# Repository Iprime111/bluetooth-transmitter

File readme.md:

# Bluetooth Audio Transmitter  

Портативный Bluetooth-передатчик для беспроводной передачи звука с аналоговых источников (3.5 мм) на наушники или колонки.  
**Цель проекта**: Интеграция проводных аудиоустройств в современные беспроводные экосистемы.

---

## 🚀 Особенности
- **Bluetooth A2DP**: Передача стереозвука с поддержкой кодеков SBC.
- **OLED-дисплей**: SSD1306 (32x64 пикселей) для управления и отображения:
  - Список доступных для подключения устройств.
  - Уровень громкости.
- **Энкодер EC11**: Интуитивное управление (выбор устройств, регулировка громкости).
- **Компактный дизайн**: Корпус 93x61x33 мм, напечатанный на 3D-принтере (PLA).
- **Автономность**: Работа от Li-Po аккумулятора 1050 мАч с зарядкой через USB-C.
- **Открытый исходный код**: Полная документация и файлы для самостоятельной сборки.

---

## 🔧 Технологии и компоненты
### Аппаратная часть
| Компонент               | Характеристики                          | Ссылка на Datasheet |
|-------------------------|-----------------------------------------|---------------------|
| Микроконтроллер         | ESP32-WROOM-32 (Bluetooth 4.2 + Wi-Fi)  | [ESP32-WROOM-32](./docs/esp32-wroom-32_datasheet_en.pdf) |
| АЦП                     | PCM1808 (24-bit, 96 kHz, SNR 112 dB)    | [PCM1808](./docs/pcm1808.pdf)  |
| Драйвер дисплея         | SSD1306 (I2C)                           | [SSD1306](./docs/SSD1306.pdf) |
| Стабилизатор питания    | ADP3338 (3.3V) / L78L05 (5V)            | [ADP3338](./docs/ADP3338.pdf), [L78L05](./docs/l78l-1.pdf) |
| Модуль заряда           | IP2326 (USB-C)                          | [IP2326](./docs/ip2326.pdf) |
| Энкодер                 | EC11                                    | [EC11](./docs/PEC11R.pdf) |

### Программная часть
- **Прошивка**: Написана на C с использованием ESP-IDF v4.4.
- **Библиотеки**:
  - `esp_a2dp` — Реализация Bluetooth A2DP Source (встроенная).
  - `i2s_audio` — Захват аудио с АЦП через I2S (встроенная).
  - `ssd1306` — Управление OLED-дисплеем (написана в рамках проекта).
  - `EC11` — Работа с энкодером (написана в рамках проекта).
- **Инструменты**:
  - `KiCad 7.0` — проектирование схемы и PCB.
  - `Autodesk Inventor` — 3D-моделирование корпуса.
  - `ESP-IDF` — сборка и отладка прошивки.

---

## 📦 Сборка устройства
### 1. Аппаратная часть
#### Схемы и PCB
- [Файлы KiCad](https://github.com/Iprime111/bluetooth-transmitter/tree/master/bluetooth-transmitter-pcb):  
  - Принципиальная схема.  
  - Разводка двухсторонней платы.  
  - Gerber-файлы для заказа на производстве.  

#### 3D-модель корпуса
- [STL и IPT-файлы](https://github.com/Iprime111/bluetooth-transmitter/tree/master/case-design):  
  - Корпус состоит из двух частей: верхняя крышка/корпус с отверстиями для дисплея/энкодера, нижняя — крышка на пазовом соединии.  
  - Рекомендуемые параметры печати: слой 0.2 мм, заполнение 15%.

---

### 2. Программная часть
#### Установка зависимостей
1. Установите [ESP-IDF v5.4](https://docs.espressif.com/projects/esp-idf/en/v5.4.1/esp32/get-started/).
2. Клонируйте репозиторий:
   ```bash
   git clone https://github.com/Iprime111/bluetooth-transmitter.git
   cd bluetooth-transmitter
   ```

#### Компиляция и прошивка
1. Подключите ESP32 через USB.
2. Соберите и загрузите проект:
   ```bash
   idf.py build
   idf.py -p /dev/ttyUSB0 flash
   ```

---

## 🎮 Использование
### Основные функции
1. **Подключение источника звука**:  
   Вставьте кабель 3.5 мм в разъем на корпусе.  
2. **Поиск устройств**:  
   - Включите устройство
   - Нажмите на кнопку энкодера для поиска устройств
   - Поворот энкодера → выбор устройства из списка.  
   - Нажмите энкодер для подключения.
   - При необходимости выберите пункт `RESTART DISCOVER` для повторного сканирования 
3. **Управление громкостью и проигрыванием**:  
   - Выберите пункт `PLAY/STOP` для воспроизведения или остановки аудио
   - Войдите в режим изменения громкости путем выбора соответствующего пункта меню. Поворотом энкодера установите желаемый уровень громкости. Для выхода повторно нажмите кнопку энкодера.  
   - Для отключения нажмите кнопку `BACK`.

---

## 📊 Технические характеристики
| Параметр                | Значение                     |
|-------------------------|------------------------------|
| Радиус действия         | До 15 м (в помещении)        |
| Автономность            | 8 часов (при 50% громкости)  |
| Задержка передачи       | < 200 мс                     |
| Частотный диапазон      | 20 Гц – 20 кГц               |

---

## 🔄 Сравнение с аналогами
| Параметр               | Наш проект             | UGREEN Transmitter     | Sennheiser BT-T100     |
|------------------------|------------------------|------------------------|------------------------|
| **Стоимость**          | ~$20 (DIY)             | ~$40                   | ~$100                  |
| **Размеры**            | 93x61x50 мм            | 80x50x20 мм            | 100x60x25 мм           |
| **Открытость**         | Полная                 | Нет                    | Нет                    |
| **Кастомизация**       | Да (код + корпус)      | Нет                    | Нет                    |

---

## 📁 Структура репозитория
```
bluetooth-transmitter/
├── components/           # Исходный код прошивки (ESP-IDF)
│   ├── audio-stream/     # Получение звука с PCM1808
│   ├── bluetooth-lib/    # GAP, AVRC, A2DP и управление подключениями
│   ├── dispatcher/       # Вспомогательные функции для асинхронной работы
│   ├── oled-display/     # Драйвер SSD1306
│   ├── main/             # Конфигурация устройства и пользовательский интерфейс
│   └── encoder/          # Обработка энкодера
├── bluetooth-transmitter-pcb/  # Схемы и PCB (KiCad)
├── case-design/          # 3D-модели корпуса (IPT, STL)
├── docs/                 # Документация
└── README.md             # Этот файл
```

---

## 📜 Лицензия
Проект распространяется под лицензией **MIT**.  
Полный текст доступен в файле [LICENSE](LICENSE).

---

## 👥 Команда
- **Владимир Чурсин**  
  - Разработка ПО, 3D-моделирование.  
  - ✉️ `chursin.vv@phystech.edu`  
  - [GitHub](https://github.com/Amlola)  
- **Максим Тимошкин**  
  - Схемотехника, сборка, тестирование.  
  - ✉️ `timoshkin.ma@phystech.edu`  
  - [GitHub](https://github.com/Iprime111)  

---

## 📸 Фото и демонстрация
**Фотография финальной версии устройства**

**Фотография прототипа**

**Демонстрация работы**:

<video width="480" height="640" controls>
  <source src="docs/demonstration.mp4" type="video/mp4">
</video>

[Ссылка, если видео не отображается на github](./docs/demonstration.mp4)

---

## 🔮 Будущие улучшения
- Добавление поддержки кодеков aptX.  
- Реализация мультиподключения (2 устройства).  
- Интеграция с мобильным приложением для настройки.  

---

**🔗 Ссылка на проект**: [GitHub](https://github.com/Iprime111/bluetooth-transmitter)

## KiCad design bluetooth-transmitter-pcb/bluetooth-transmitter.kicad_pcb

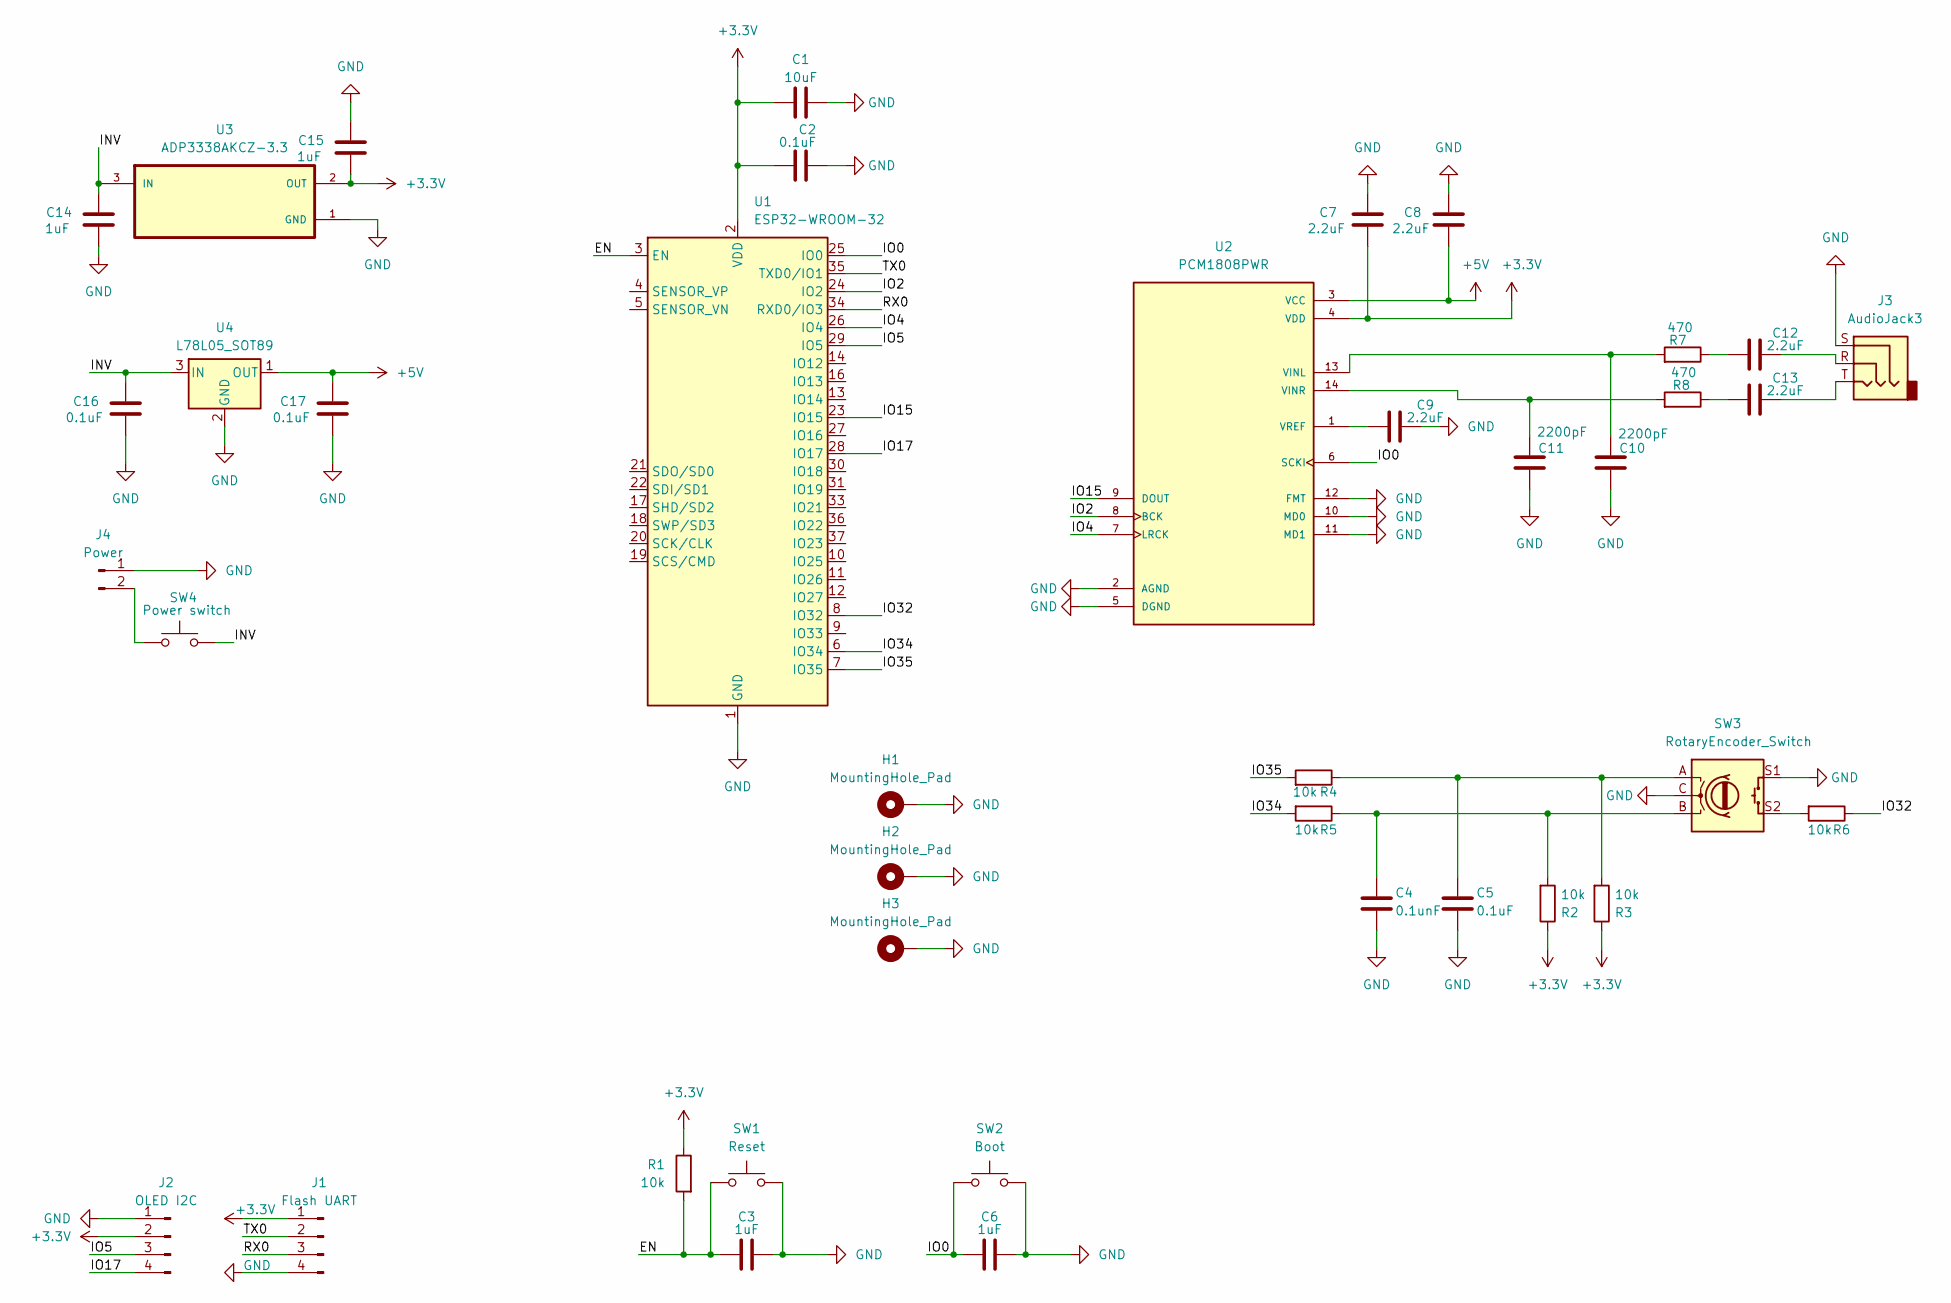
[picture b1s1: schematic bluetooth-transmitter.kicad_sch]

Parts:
C1: 10uF; C_0603_1608Metric_Pad1.08x0.95mm_HandSolder
C2, C5, C16, C17: 0.1uF; C_0603_1608Metric_Pad1.08x0.95mm_HandSolder
C3, C6, C14, C15: 1uF; C_0603_1608Metric_Pad1.08x0.95mm_HandSolder
C4: 0.1unF; C_0603_1608Metric_Pad1.08x0.95mm_HandSolder
C7, C8, C9, C12, C13: 2.2uF; C_0603_1608Metric_Pad1.08x0.95mm_HandSolder
C10, C11: 2200pF; C_0603_1608Metric_Pad1.08x0.95mm_HandSolder
H1, H2, H3: MountingHole_Pad; MountingHole_2.2mm_M2_ISO7380_Pad_TopOnly
J1: Flash UART; PinHeader_1x04_P2.54mm_Vertical
J2: OLED I2C; PinHeader_1x04_P2.54mm_Vertical
J3: AudioJack3; Jack_3.5mm_CUI_SJ1-3533NG_Horizontal
J4: Power; PinSocket_1x02_P2.54mm_Vertical
R1, R2, R3, R4, R5, R6: 10k; R_1206_3216Metric_Pad1.30x1.75mm_HandSolder
R7, R8: 470; R_1206_3216Metric_Pad1.30x1.75mm_HandSolder
SW1: Reset; SW_PUSH_6mm_H4.3mm
SW2: Boot; SW_PUSH_6mm_H4.3mm
SW3: RotaryEncoder_Switch; RotaryEncoder_Alps_EC11E-Switch_Vertical_H20mm
SW4: Power switch; PinSocket_1x02_P2.54mm_Vertical
U1: ESP32-WROOM-32
U2: PCM1808PWR; SOP65P640X120-14N; PARTREV B
U3: ADP3338AKCZ-3.3; SOT-223-3_TabPin2
U4: L78L05_SOT89; SOT-89-3

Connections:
+3.3V: C1.2, C2.1, C7.2, C15.2, J1.1, J2.2, R1.1, R2.1, R3.1, U1.2 (VDD), U2.4 (VDD), U3.2 (OUT)
+5V: C8.2, C17.1, U2.3 (VCC), U4.1 (OUT)
/EN: C3.2, R1.2, SW1.2, U1.3 (EN)
/INV: C14.1, C16.1, SW4.2, U3.3 (IN), U4.3 (IN)
/IO0: C6.2, SW2.2, U1.25 (IO0), U2.6 (SCKI)
/IO2: U1.24 (IO2), U2.8 (BCK)
/IO4: U1.26 (IO4), U2.7 (LRCK)
/IO5: J2.3, U1.29 (IO5)
/IO15: U1.23 (IO15), U2.9 (DOUT)
/IO17: J2.4, U1.28 (IO17)
/IO32: R6.1, U1.8 (IO32)
/IO34: R5.2, U1.6 (IO34)
/IO35: R4.2, U1.7 (IO35)
/RX0: J1.3, U1.34 (RXD0/IO3)
/TX0: J1.2, U1.35 (TXD0/IO1)
GND: C1.1, C2.2, C3.1, C4.2, C5.2, C6.1, C7.1, C8.1, C9.2, C10.1, C11.1, C14.2, C15.1, C16.2, C17.2, H1.1, H2.1, H3.1, J1.4, J2.1, J3.S, J4.1, SW1.1, SW2.1, SW3.C, SW3.S1, U1.1 (GND), U1.15 (GND), U1.38 (GND), U1.39 (GND), U2.2 (AGND), U2.5 (DGND), U2.10 (MD0), U2.11 (MD1), U2.12 (FMT), U3.1 (GND), U4.2 (GND)
unnamed: C4.1, R2.2, R5.1, SW3.B
unnamed: C5.1, R3.2, R4.1, SW3.A
unnamed: C12.1, R7.1
unnamed: C12.2, J3.R
unnamed: C13.1, R8.1
unnamed: C13.2, J3.T
unnamed: J4.2, SW4.1
unnamed: R6.2, SW3.S2
unnamed: C10.2, R7.2, U2.13 (VINL)
unnamed: C11.2, R8.2, U2.14 (VINR)
unnamed: C9.1, U2.1 (VREF)

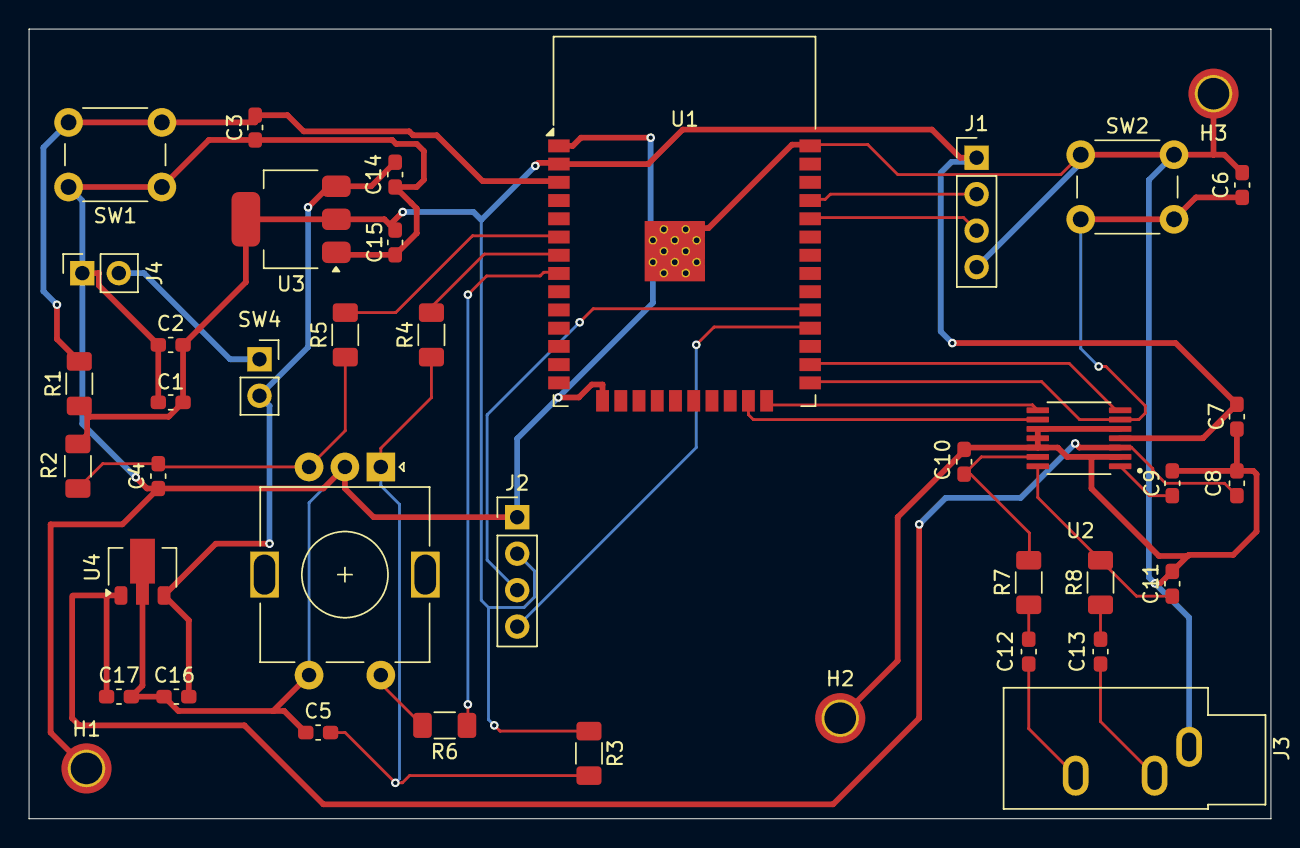
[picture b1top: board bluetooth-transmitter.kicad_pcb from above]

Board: 2 copper layers, 86.5 x 55.0 mm, 40 parts (0 on the bottom side), 27 nets.

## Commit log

2025-04-16 Add dispatcher and bt_lib components
    Add first working version of a2dp transmission (white noise)
2025-04-19 Add oled display library with text/pixel displaying
2025-04-23 Add encoder lib with button debounce support
    Fix text displaying bug in the display lib
2025-04-24 Add simple device picking menu. Add bt callbacks
2025-04-25 Add full menu and audio control
    Add volume level control, playing/stopping audio stream, rescanning
2025-04-27 Add working audio callback for A2DP
    Add input audio stream capabilities with PCM1808 support
2025-04-27 Add volume changing event
    Support correct volume level displaying when controlling from peer.
    Change static const variables to macros to force binary file size
    optimizations.
2025-04-29 Change GPIO ports to be in correlation with PCB
2025-04-29 Update PCB to last version
    Add power chain and PCM1808 to schematic. Create PCB from shecmatic.
    Make PCB ready for production.
2025-05-11 Update ports, enable button pullup
2025-05-11 Update pcb
2025-05-14 Add 3D models files
2025-05-14 Add readme and docs
2025-05-14 Rename 3d models folder
2025-05-14 Create LICENSE
2025-05-14 Add photo
2025-05-14 Fix readme
2025-05-14 Remove keys-design folder
2025-05-14 Fix video in readme

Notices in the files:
readme.md:
License: MIT
